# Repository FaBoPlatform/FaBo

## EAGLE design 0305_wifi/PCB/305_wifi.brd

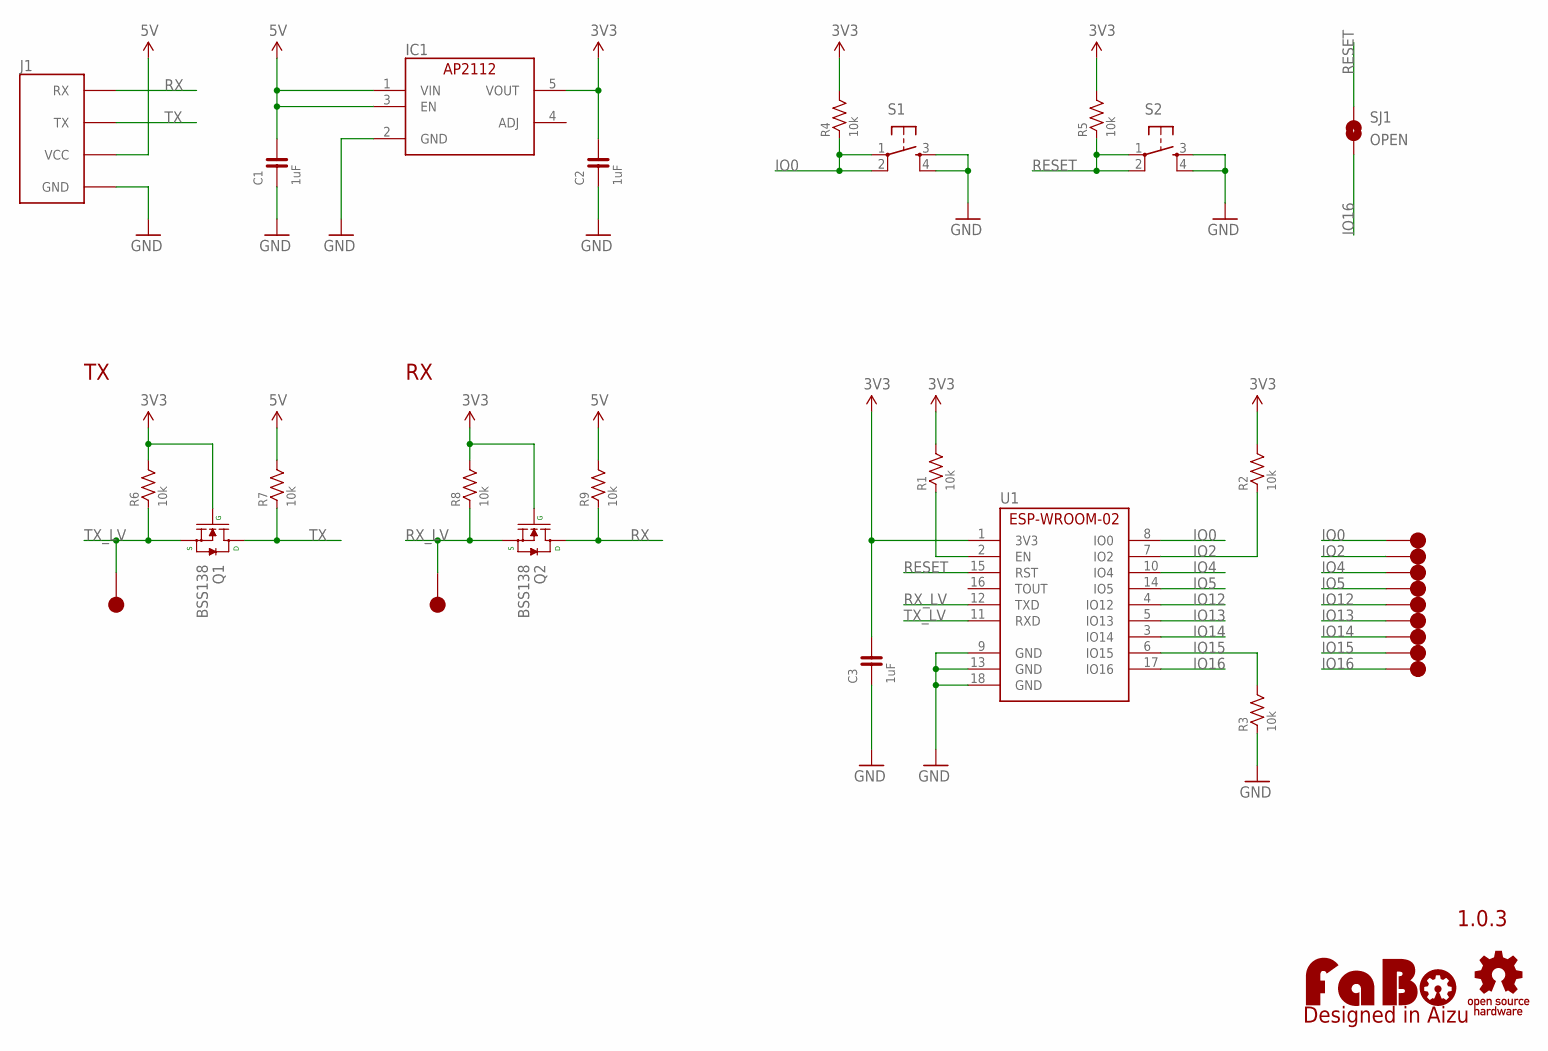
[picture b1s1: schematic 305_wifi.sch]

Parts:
C1, C2, C3: 1uF; 0603
IC1: AP2112K-3.3TRG1; SOT-23-5
J1: FABO_BRICK_SERIAL-2_HOLE; FABO_BRICK_SERIAL_2HOLE
LOGO1: LOGO_FABO-M_BOTTOM; LOGO_FABO_M_BOTTOM
Q1, Q2: BSS138; SOT23-3
R1, R2, R3, R4, R5: 10k; 0603
R6, R7, R8, R9: 10k; 0603-NARROW
S1, S2: TACT-SWITCH-SMD_KMR2; KMR2
SJ1: OPEN; SMD-JUMPER-2-OPEN
TP1, TP2, TP3, TP4, TP5, TP6, TP7, TP8, TP9, TP10, TP11: TP-15
U1: ES-ESPWROOM02
U$1: LOGO_OSHW-M_BOTTOM; LOGO_OSHW_M_BOTTOM

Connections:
3V3: C2.2, C3.2, IC1.5 (VOUT), Q1.1 (G), Q2.1 (G), R1.2, R2.2, R4.2, R5.2, R6.2, R8.2, U1.1 (3V3)
5V: C1.2, IC1.1 (VIN), IC1.3 (EN), J1.VCC, R7.2, R9.2
EN: R1.1, U1.2 (EN)
GND: C1.1, C2.1, C3.1, IC1.2 (GND), J1.GND, R3.1, S1.3, S1.4, S2.3, S2.4, U1.9 (GND), U1.13 (GND), U1.18 (GND)
IO0: R4.1, S1.1, S1.2, TP1.1, U1.8 (IO0)
IO2: R2.1, TP2.1, U1.7 (IO2)
IO4: TP3.1, U1.10 (IO4)
IO5: TP4.1, U1.14 (IO5)
IO12: TP5.1, U1.4 (IO12)
IO13: TP6.1, U1.5 (IO13)
IO14: TP7.1, U1.3 (IO14)
IO15: R3.2, TP8.1, U1.6 (IO15)
IO16: SJ1.2, TP9.1, U1.17 (IO16)
RESET: R5.1, S2.1, S2.2, SJ1.1, U1.15 (RST)
RX: J1.RX, Q2.3 (D), R9.1
RX_LV: Q2.2 (S), R8.1, TP10.1, U1.12 (TXD)
TX: J1.TX, Q1.3 (D), R7.1
TX_LV: Q1.2 (S), R6.1, TP11.1, U1.11 (RXD)

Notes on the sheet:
1.0.3

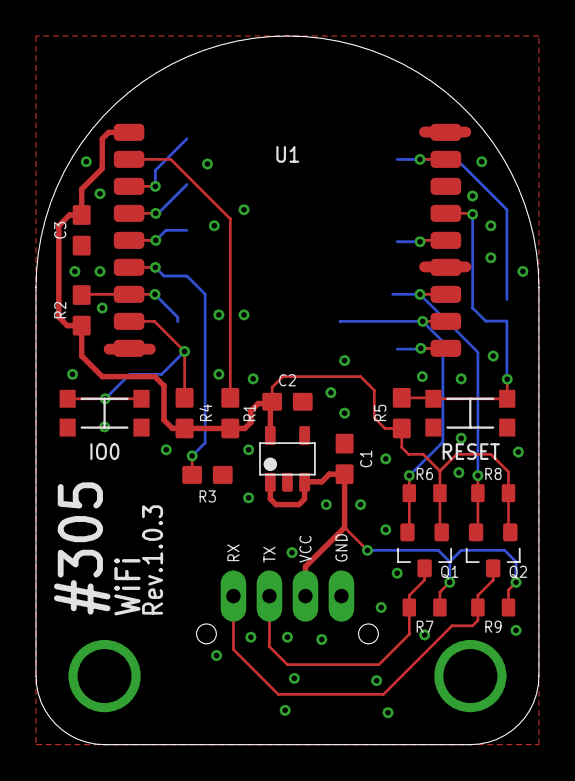
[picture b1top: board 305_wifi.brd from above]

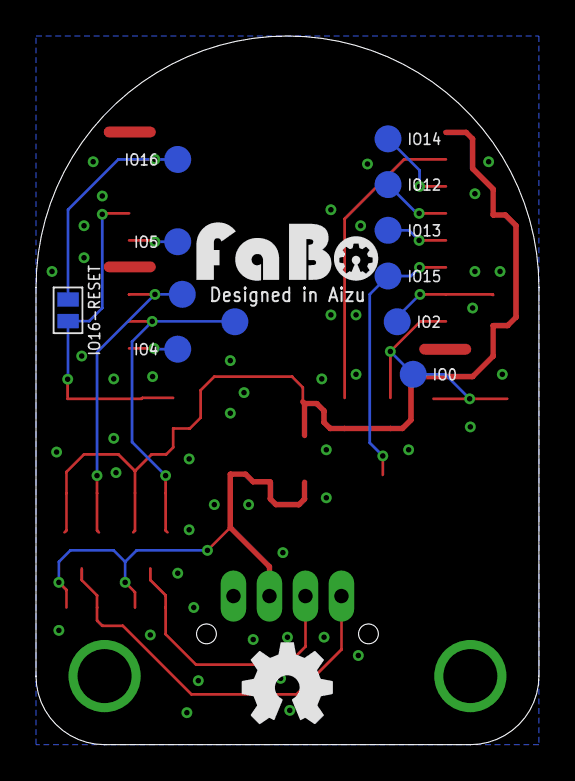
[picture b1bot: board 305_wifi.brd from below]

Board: 2 copper layers, 27.9 x 39.4 mm, 33 parts (12 on the bottom side), 18 nets.

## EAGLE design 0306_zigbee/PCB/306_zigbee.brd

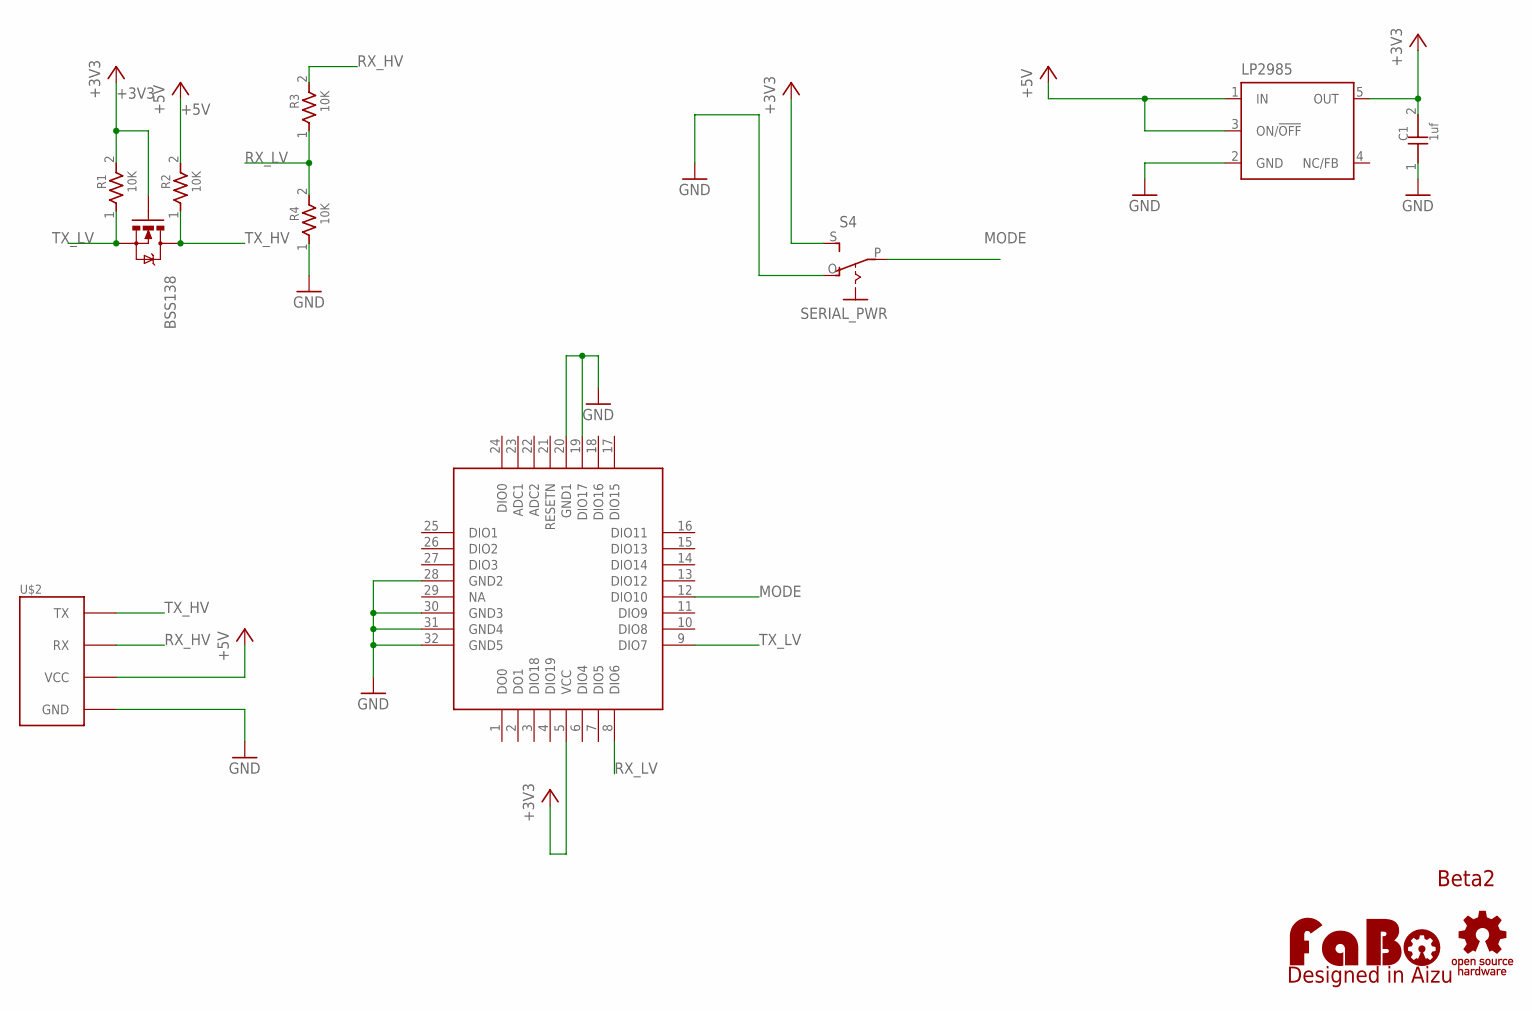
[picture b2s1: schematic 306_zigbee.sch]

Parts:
BSS138: MOSFET-NCHANNELSMD; SOT23-3
C1: 1uf; 0603
LOGO1: LOGO_FABO-M; LOGO_FABO_M
LP2985: LP2985-XXDBVR33; SOT23-DBV
R1, R2, R3, R4: 10K; 0603
S4: SERIAL_PWR; EG1218
U$2: BRICK_SERIAL
U$3: TOCOS-TWE001L
U$4: LOGO_OSHW-M_BOTTOM; LOGO_OSHW_M_BOTTOM

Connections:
+3V3: BSS138.1 (G), C1.2, LP2985.5 (OUT), R1.2, S4.S, U$3.5 (VCC)
+5V: LP2985.1 (IN), LP2985.3 (ON/!OFF), R2.2, U$2.VCC
GND: C1.1, LP2985.2 (GND), R4.1, S4.O, U$2.GND, U$3.19 (DIO17), U$3.20 (GND1), U$3.28 (GND2), U$3.30 (GND3), U$3.31 (GND4), U$3.32 (GND5)
MODE: S4.P, U$3.12 (DIO10)
RX_HV: R3.2, U$2.RX
RX_LV: R3.1, R4.2, U$3.8 (DIO6)
TX_HV: BSS138.3 (D), R2.1, U$2.TX
TX_LV: BSS138.2 (S), R1.1, U$3.9 (DIO7)

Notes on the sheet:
Beta2

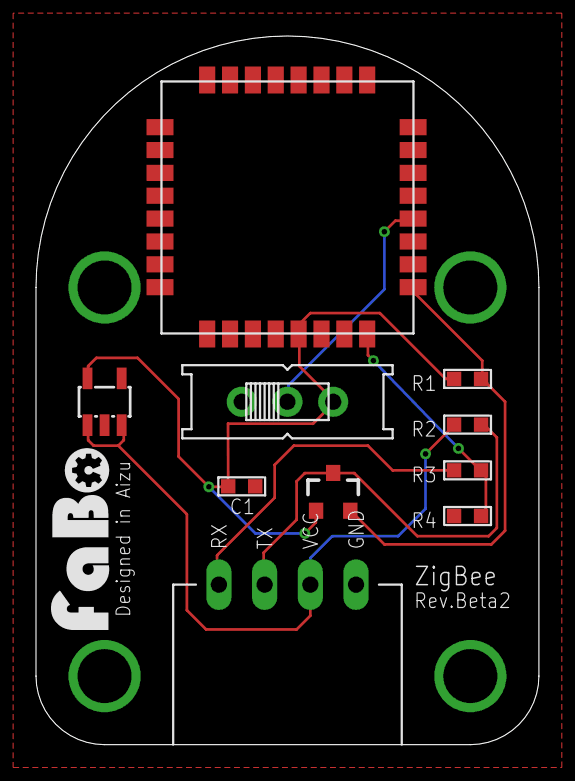
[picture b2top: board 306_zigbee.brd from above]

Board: 2 copper layers, 27.9 x 39.4 mm, 12 parts (0 on the bottom side), 8 nets.

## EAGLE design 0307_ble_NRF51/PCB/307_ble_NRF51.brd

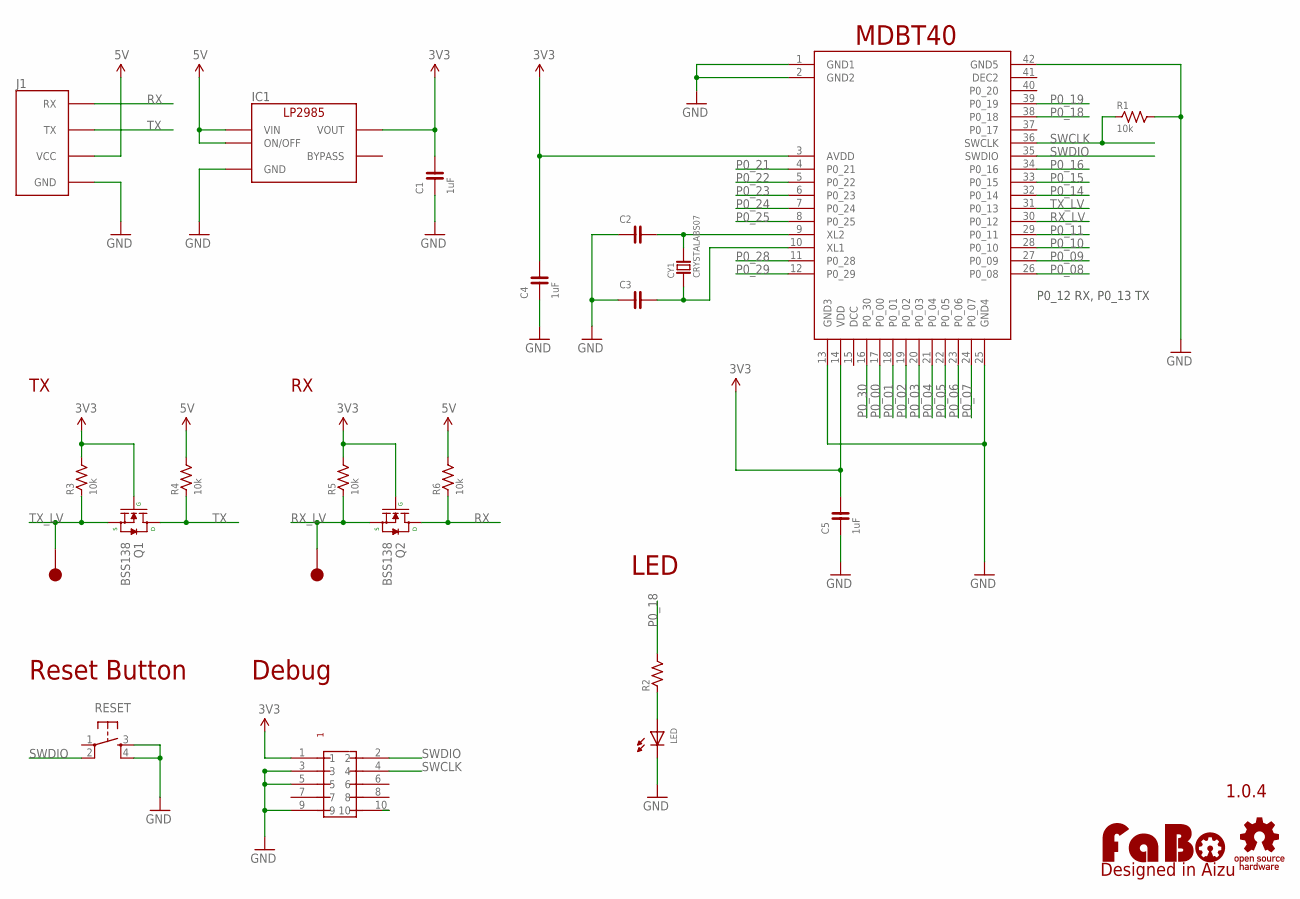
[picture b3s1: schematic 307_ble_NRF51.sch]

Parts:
C1, C4, C5: 1uF; 0603-NARROW
C2, C3: CAPACITOR-0603_NARROW; 0603-NARROW
CY1: CRYSTALABS07; ABRACOM-ABS07-32.768KHZ
IC1: LP2985-33DBV; SOT-23-5
J1: FABO_BRICK_SERIAL
LED: LED-0603; 0603
LOGO1: LOGO_FABO-M_BOTTOM; LOGO_FABO_M_BOTTOM
Q1, Q2: BSS138; SOT23-3
R1, R3, R4, R5, R6: 10k; 0603-NARROW
R2: RESISTOR-0603-NARROW; 0603-NARROW
RESET: TACT-SWITCH-SMD_KMR2; KMR2
TP10, TP11: TP-15
U$2: LOGO_OSHW-M_BOTTOM; LOGO_OSHW_M_BOTTOM
U$7: RAYTAC-MDBT40
U$8: PIN-HEADER-SMT(1.27MM)2X5

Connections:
3V3: C1.2, C4.2, C5.2, IC1.5 (VOUT), Q1.1 (G), Q2.1 (G), R3.2, R5.2, U$7.3 (AVDD), U$7.14 (VDD), U$8.1
5V: IC1.1 (VIN), IC1.3 (ON/OFF), J1.VCC, R4.2, R6.2
GND: C1.1, C2.1, C3.1, C4.1, C5.1, IC1.2 (GND), J1.GND, LED.CATHODE, R1.2, RESET.3, RESET.4, U$7.1 (GND1), U$7.2 (GND2), U$7.13 (GND3), U$7.25 (GND4), U$7.42 (GND5), U$8.3, U$8.5, U$8.9
unnamed: LED.ANODE, R2.1
unnamed: C2.2, CY1.P$2, U$7.9 (XL2)
unnamed: C3.2, CY1.P$1, U$7.10 (XL1)
P0_00: U$7.17 (P0_00)
P0_01: U$7.18 (P0_01)
P0_02: U$7.19 (P0_02)
P0_03: U$7.20 (P0_03)
P0_04: U$7.21 (P0_04)
P0_05: U$7.22 (P0_05)
P0_06: U$7.23 (P0_06)
P0_07: U$7.24 (P0_07)
P0_08: U$7.26 (P0_08)
P0_09: U$7.27 (P0_09)
P0_10: U$7.28 (P0_10)
P0_11: U$7.29 (P0_11)
P0_14: U$7.32 (P0_14)
P0_15: U$7.33 (P0_15)
P0_16: U$7.34 (P0_16)
P0_18: R2.2, U$7.38 (P0_18)
P0_19: U$7.39 (P0_19)
P0_21: U$7.4 (P0_21)
P0_22: U$7.5 (P0_22)
P0_23: U$7.6 (P0_23)
P0_24: U$7.7 (P0_24)
P0_25: U$7.8 (P0_25)
P0_28: U$7.11 (P0_28)
P0_29: U$7.12 (P0_29)
P0_30: U$7.16 (P0_30)
RESET: U$8.10
RX: J1.RX, Q2.3 (D), R6.1
RX_LV: Q2.2 (S), R5.1, TP10.1, U$7.30 (P0_12)
SWCLK: R1.1, U$7.36 (SWCLK), U$8.4
SWDIO: RESET.2, U$7.35 (SWDIO), U$8.2
TX: J1.TX, Q1.3 (D), R4.1
TX_LV: Q1.2 (S), R3.1, TP11.1, U$7.31 (P0_13)

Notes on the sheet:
1.0.4
Reset Button
MDBT40
LED
Debug
P0_12 RX, P0_13 TX

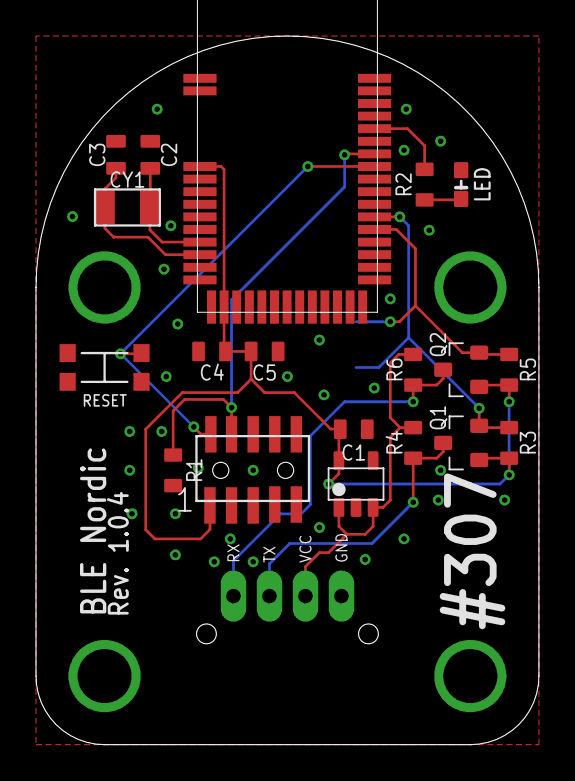
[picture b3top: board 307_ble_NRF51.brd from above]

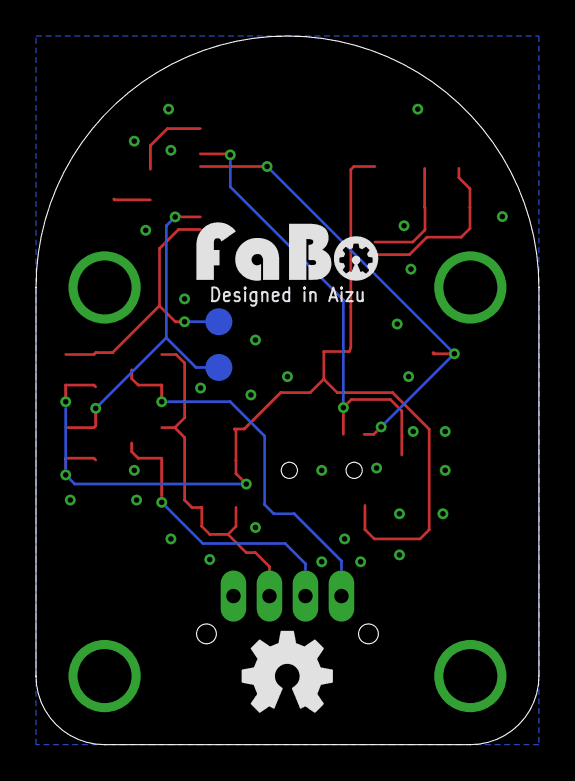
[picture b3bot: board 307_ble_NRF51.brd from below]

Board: 2 copper layers, 27.9 x 39.4 mm, 24 parts (2 on the bottom side), 13 nets.

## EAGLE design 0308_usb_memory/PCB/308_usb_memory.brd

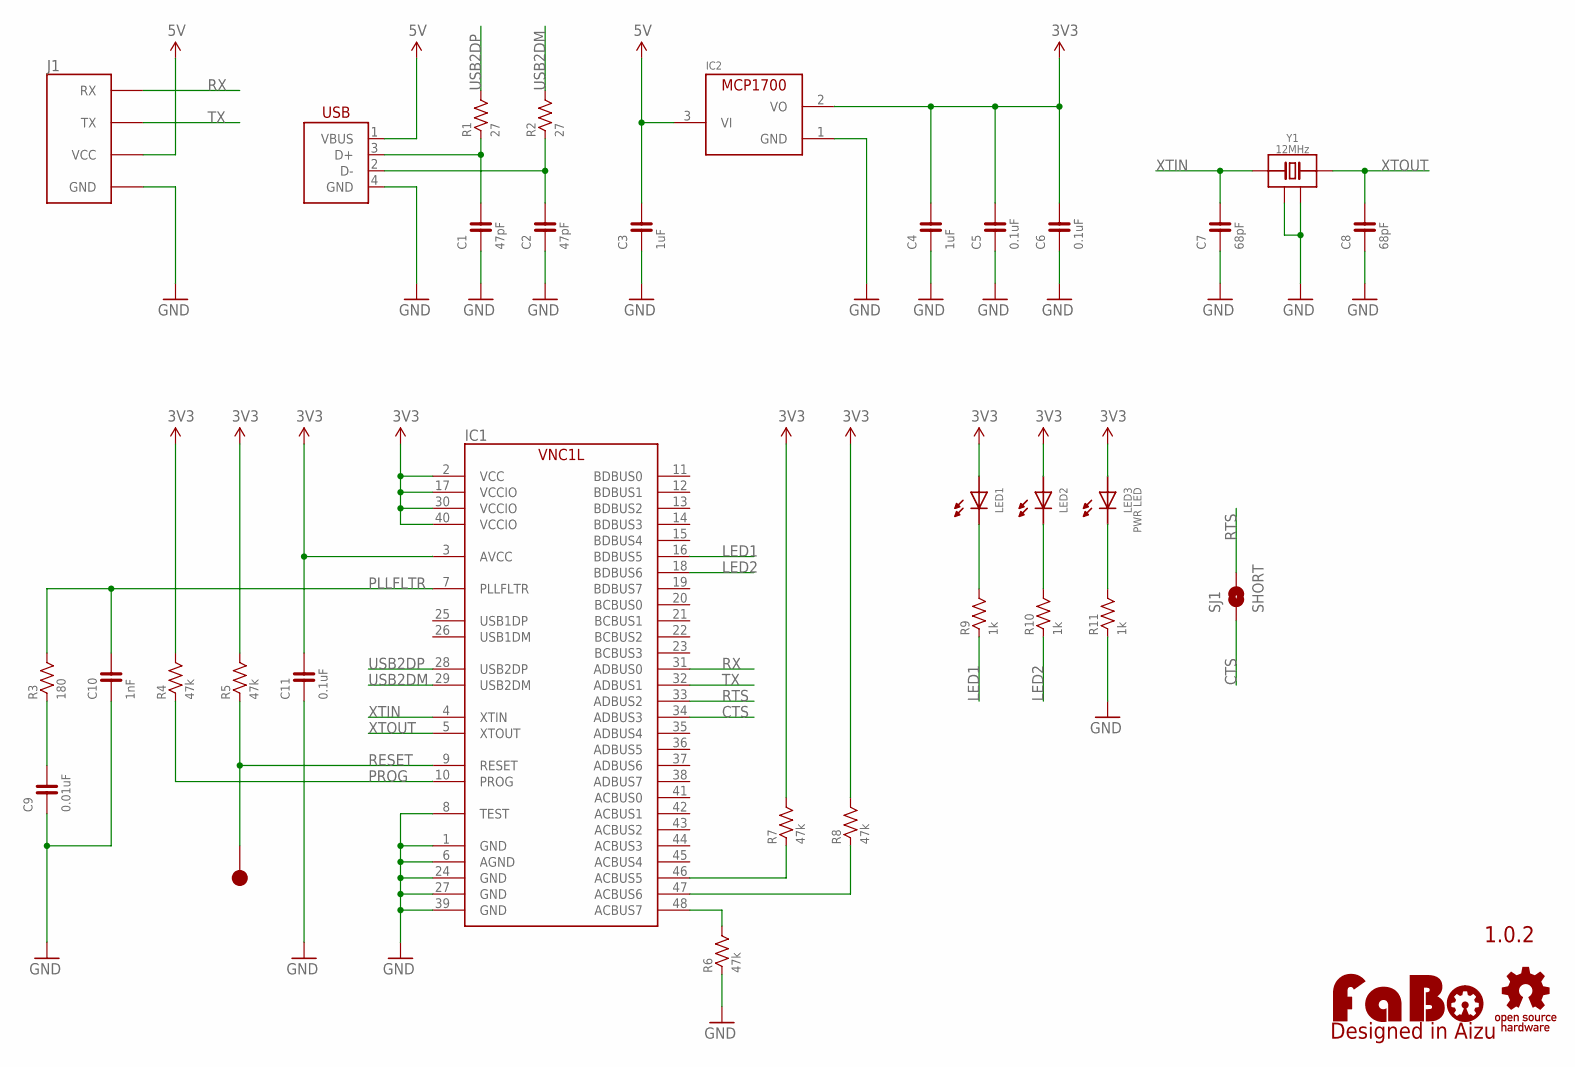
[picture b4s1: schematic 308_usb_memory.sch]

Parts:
C1, C2: 47pF; 0603-NARROW
C3, C4: 1uF; 0603-NARROW
C5, C6, C11: 0.1uF; 0603-NARROW
C7, C8: 68pF; 0603-NARROW
C9: 0.01uF; 0603-NARROW
C10: 1nF; 0603-NARROW
IC1: VNC1L-1A; LQFP-48
IC2: MCP1700T-3302TT; SOT-23
J1: FABO_BRICK_SERIAL-2_HOLE; FABO_BRICK_SERIAL_2HOLE
LED1, LED2: LED-0603-NARROW; 0603-NARROW
LED3: PWR LED; 0603-NARROW
LOGO1: LOGO_FABO-M_BOTTOM; LOGO_FABO_M_BOTTOM
R1, R2: 27; 0603-NARROW
R3: 180; 0603-NARROW
R4, R5, R6, R7, R8: 47k; 0603-NARROW
R9, R10, R11: 1k; 0603-NARROW
SJ1: SHORT; SMD-JUMPER-2-SHORT
TP1: TP-15
U$2: LOGO_OSHW-M_BOTTOM; LOGO_OSHW_M_BOTTOM
USB1: USB-B_PTH; USB-4AF103BS
Y1: 12MHz; ECS-12MHZ

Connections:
3V3: C4.2, C5.2, C6.2, C11.2, IC1.2 (VCC), IC1.3 (AVCC), IC1.17 (VCCIO), IC1.30 (VCCIO), IC1.40 (VCCIO), IC2.2 (VO), LED1.ANODE, LED2.ANODE, LED3.ANODE, R4.2, R5.2, R7.2, R8.2
5V: C3.2, IC2.3 (VI), J1.VCC, USB1.1 (VBUS)
ACBUS5: IC1.46 (ACBUS5), R7.1
ACBUS6: IC1.47 (ACBUS6), R8.1
ACBUS7: IC1.48 (ACBUS7), R6.2
CTS: IC1.34 (ADBUS3), SJ1.2
GND: C1.1, C2.1, C3.1, C4.1, C5.1, C6.1, C7.1, C8.1, C9.1, C10.1, C11.1, IC1.1 (GND), IC1.6 (AGND), IC1.8 (TEST), IC1.24 (GND), IC1.27 (GND), IC1.39 (GND), IC2.1 (GND), J1.GND, R6.1, R11.1, USB1.4 (GND), Y1.2 (GND), Y1.4 (GND)
LED1: IC1.16 (BDBUS5), R9.1
LED2: IC1.18 (BDBUS6), R10.1
unnamed: C9.2, R3.1
unnamed: C1.2, R1.1, USB1.3 (D+)
unnamed: C2.2, R2.1, USB1.2 (D-)
unnamed: LED2.CATHODE, R10.2
unnamed: LED1.CATHODE, R9.2
unnamed: LED3.CATHODE, R11.2
PLLFLTR: C10.2, IC1.7 (PLLFLTR), R3.2
PROG: IC1.10 (PROG), R4.1
RESET: IC1.9 (RESET), R5.1, TP1.1
RTS: IC1.33 (ADBUS2), SJ1.1
RX: IC1.31 (ADBUS0), J1.RX
TX: IC1.32 (ADBUS1), J1.TX
USB2DM: IC1.29 (USB2DM), R2.2
USB2DP: IC1.28 (USB2DP), R1.2
XTIN: C7.2, IC1.4 (XTIN), Y1.1 (IO)
XTOUT: C8.2, IC1.5 (XTOUT), Y1.3 (IO)

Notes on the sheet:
1.0.2

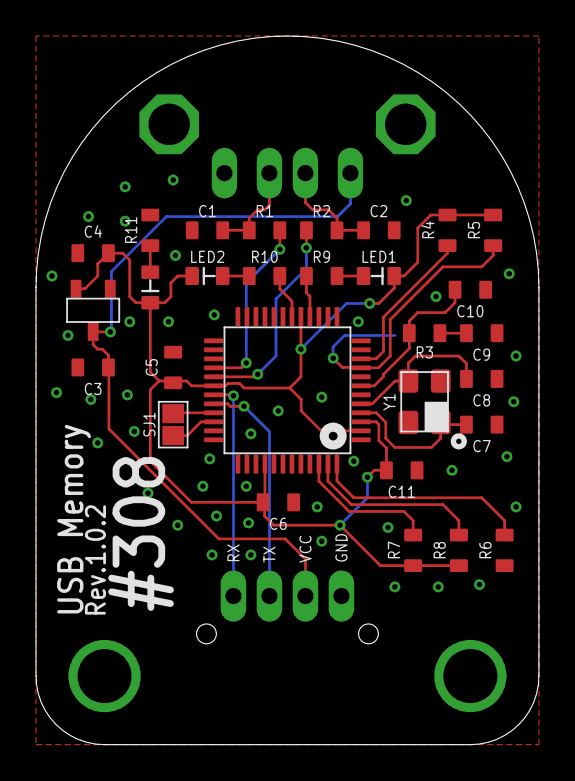
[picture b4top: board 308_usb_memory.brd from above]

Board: 2 copper layers, 27.9 x 39.4 mm, 34 parts (1 on the bottom side), 25 nets.

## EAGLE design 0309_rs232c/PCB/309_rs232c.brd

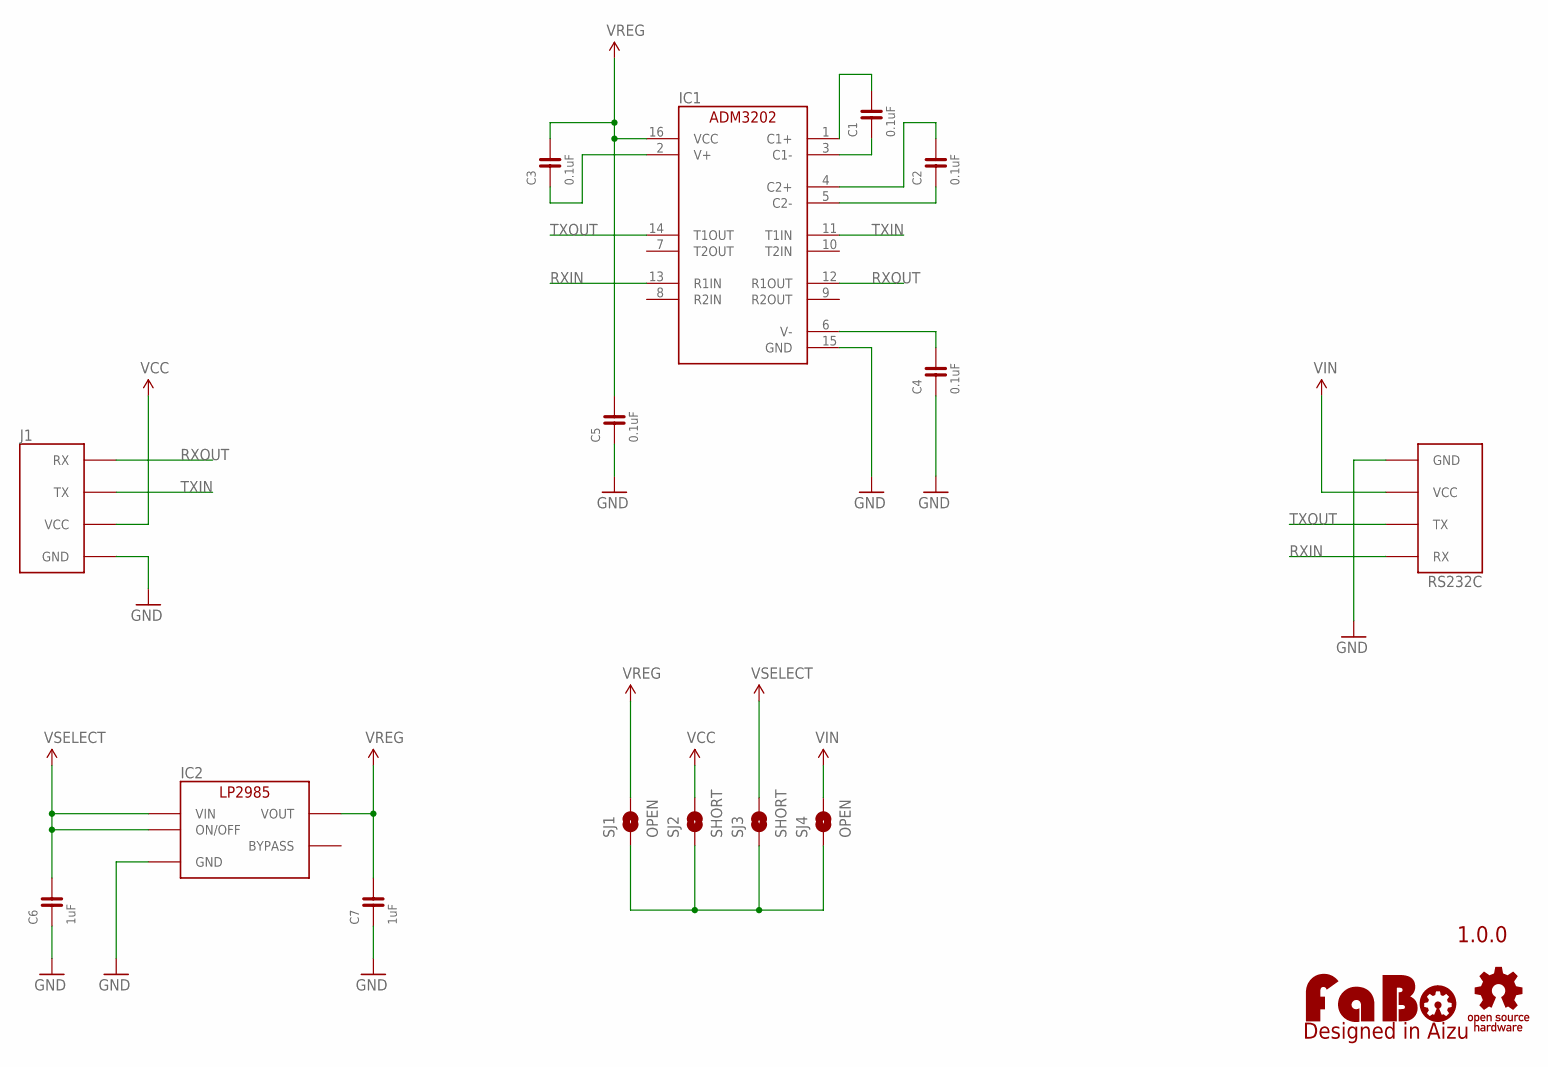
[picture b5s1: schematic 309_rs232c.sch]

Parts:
C1, C2, C3, C4, C5: 0.1uF; 0603-NARROW
C6, C7: 1uF; 0603-NARROW
IC1: ADM3202ARU; TSSOP-16
IC2: LP2985-33DBV; SOT-23-5
J1: FABO_BRICK_SERIAL
LOGO1: LOGO_FABO-M_BOTTOM; LOGO_FABO_M_BOTTOM
RS232C: FABO_BRICK_SERIAL-S04B-PASK-2_LONG; FABO_BRICK_SERIAL_S04B-PASK-2_LONG
SJ1, SJ4: OPEN; SMD-JUMPER-2-OPEN
SJ2, SJ3: SHORT; SMD-JUMPER-2-SHORT
U$2: LOGO_OSHW-M_BOTTOM; LOGO_OSHW_M_BOTTOM

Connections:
GND: C4.1, C5.1, C6.1, C7.1, IC1.15 (GND), IC2.2 (GND), J1.GND, RS232C.GND
unnamed: SJ1.2, SJ2.2, SJ3.2, SJ4.2
unnamed: C1.1, IC1.3 (C1-)
unnamed: C1.2, IC1.1 (C1+)
unnamed: C2.1, IC1.5 (C2-)
unnamed: C2.2, IC1.4 (C2+)
unnamed: C3.1, IC1.2 (V+)
unnamed: C4.2, IC1.6 (V-)
RXIN: IC1.13 (R1IN), RS232C.RX
RXOUT: IC1.12 (R1OUT), J1.RX
TXIN: IC1.11 (T1IN), J1.TX
TXOUT: IC1.14 (T1OUT), RS232C.TX
VCC: J1.VCC, SJ2.1
VIN: RS232C.VCC, SJ4.1
VREG: C3.2, C5.2, C7.2, IC1.16 (VCC), IC2.5 (VOUT), SJ1.1
VSELECT: C6.2, IC2.1 (VIN), IC2.3 (ON/OFF), SJ3.1

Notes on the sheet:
1.0.0

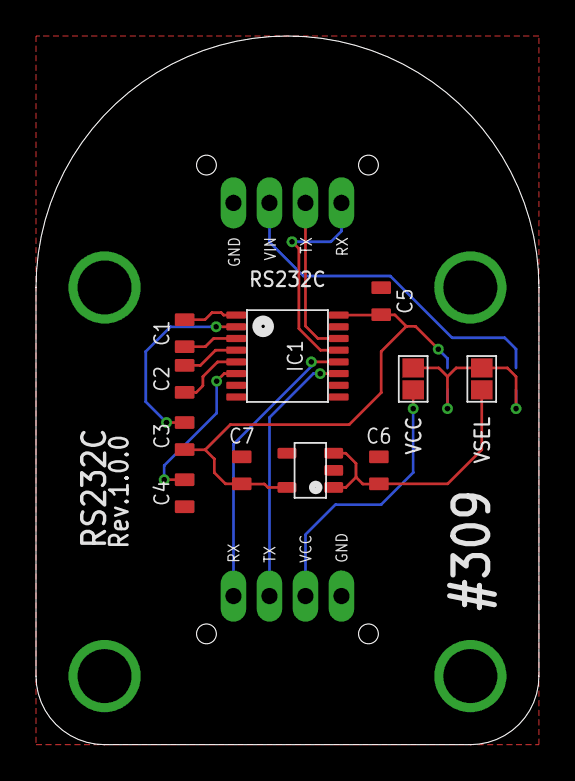
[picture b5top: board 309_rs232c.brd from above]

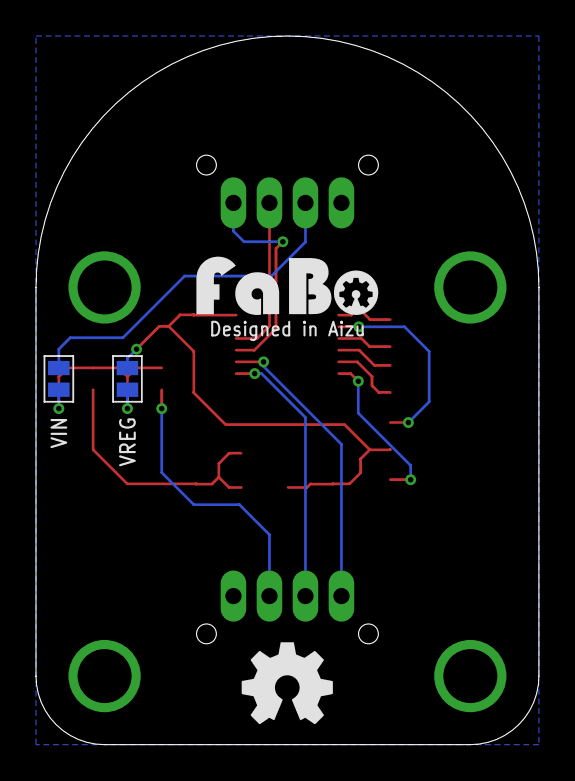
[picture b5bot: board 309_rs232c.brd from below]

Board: 2 copper layers, 27.9 x 39.4 mm, 17 parts (2 on the bottom side), 16 nets.

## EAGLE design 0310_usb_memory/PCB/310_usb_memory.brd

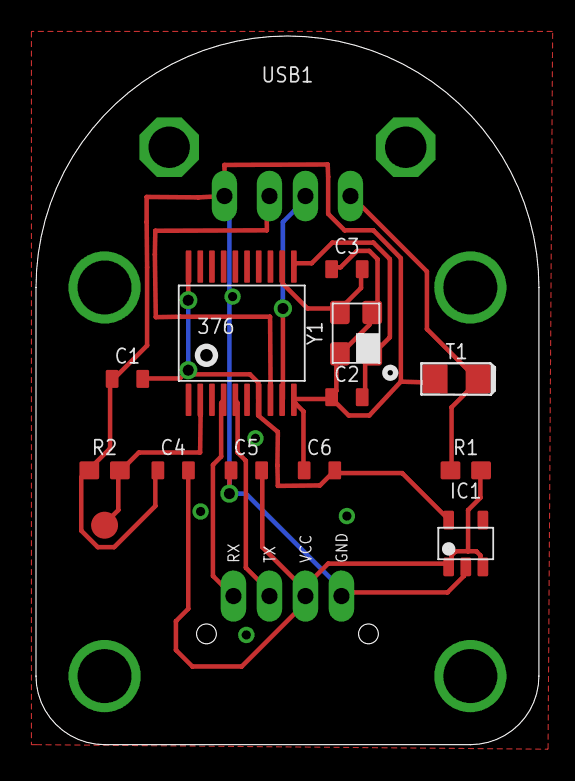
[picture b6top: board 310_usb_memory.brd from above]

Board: 2 copper layers, 27.9 x 39.4 mm, 15 parts (0 on the bottom side), 11 nets.

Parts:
376: CH376T; SSOP-20
C1, C5, C6: 0.1uF; 0603-NARROW
C2, C3: 22pF; 0603-NARROW
C4: 10uF; 0603-NARROW
IC1: SOT-23-5
J1: FABO_BRICK_SERIAL
R1: 2; 0603
R2: 4.7K; 0603
T1: 10uF; 1206-TANTULM
TP1: TP-15
USB1: USB-4AF103BS
Y1: 12MHz; ECS-12MHZ

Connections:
3V3: 376.7, 376.20, C1.2, C6.2, IC1.5
5V: C4.2, C5.2, IC1.1, IC1.3, J1.VCC, R1.2
D+: 376.8, USB1.3
D-: 376.9, USB1.2
GND: 376.10, C1.1, C2.1, C3.1, C4.1, C5.1, C6.1, IC1.2, J1.GND, R2.1, T1.-, USB1.4, Y1.2, Y1.4
unnamed: R1.1, T1.+, USB1.1
RESET: 376.2, R2.2, TP1.1
RX: 376.4, J1.RX
TX: 376.5, J1.TX
XTIN: 376.11, C2.2, Y1.1
XTOUT: 376.12, C3.2, Y1.3

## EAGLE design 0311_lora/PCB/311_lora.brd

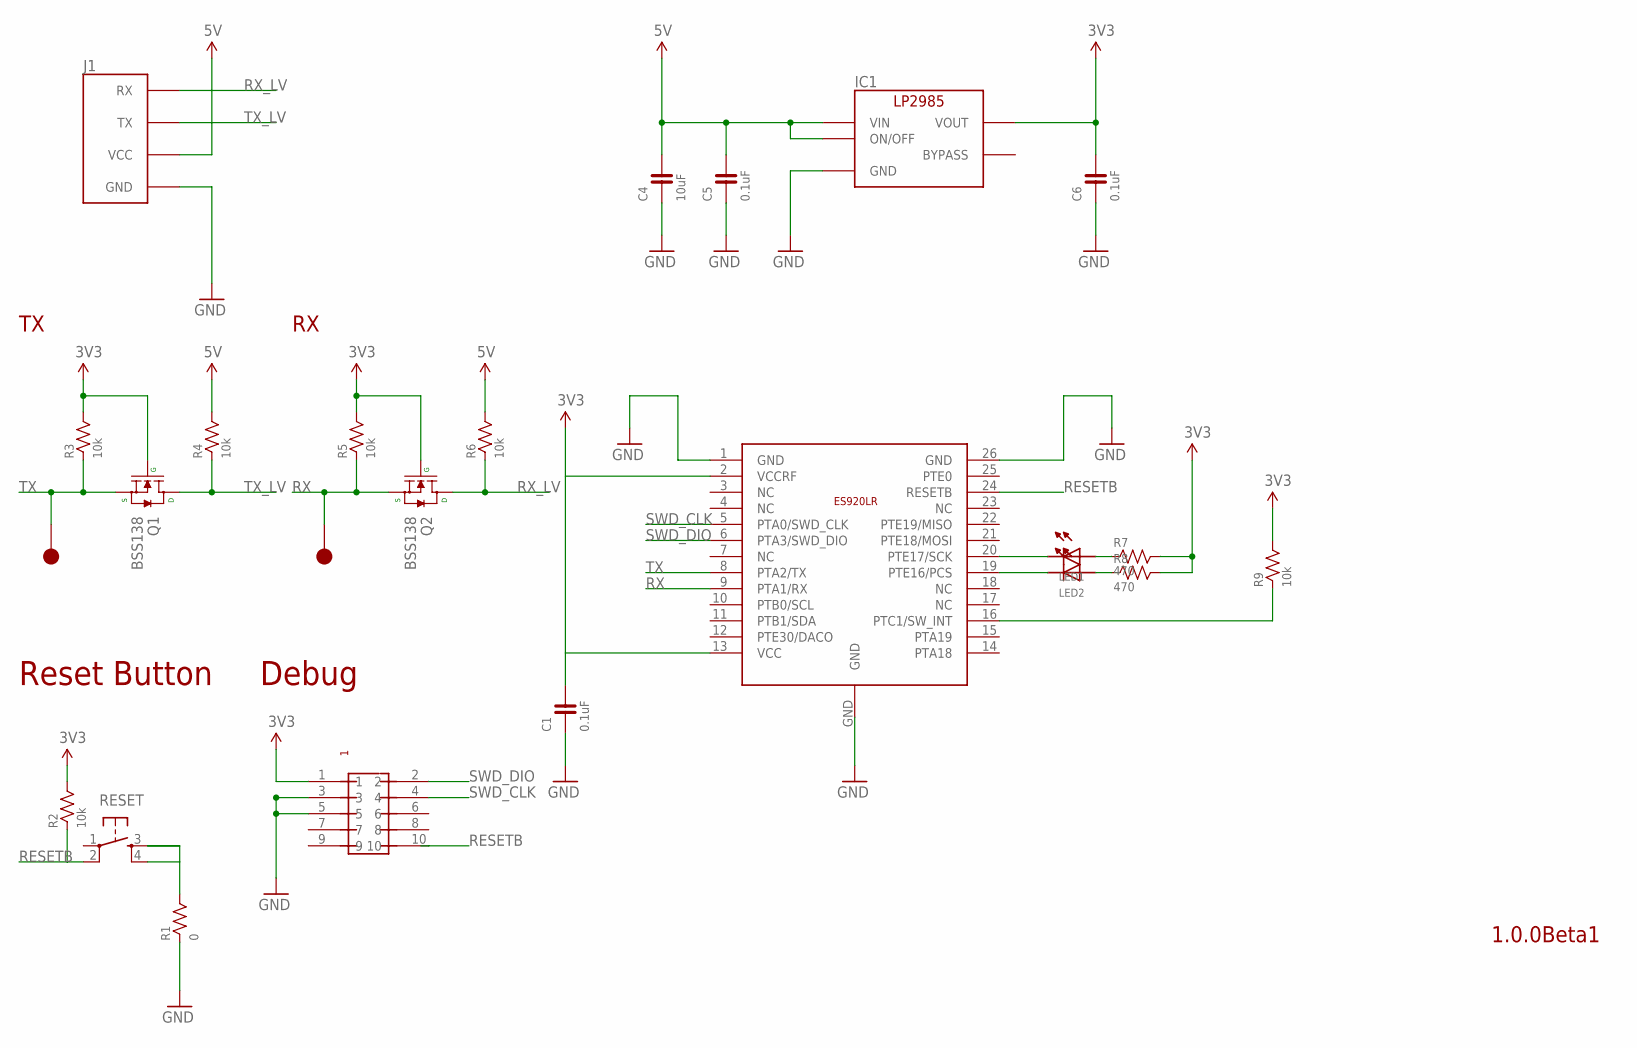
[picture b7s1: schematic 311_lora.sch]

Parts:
C1, C5, C6: 0.1uF; 0603-NARROW
C4: 10uF; 0603-NARROW
IC1: LP2985-33DBV; SOT-23-5
J1: FABO_BRICK_SERIAL-LONGER; FABO_BRICK_SERIAL_LONGER
LED1, LED2: LED-0603; 0603
Q1, Q2: BSS138; SOT23-3
R1: 0; 0603-NARROW
R2, R3, R4, R5, R6, R9: 10k; 0603-NARROW
R7, R8: 470; 0603-NARROW
RESET: TACT-SWITCH-SMD_KMR2; KMR2
TP10, TP11: TP-15
U$2: ES920LR
U$8: PIN-HEADER-SMT(1.27MM)2X5

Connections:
3V3: C1.2, C6.2, IC1.5 (VOUT), Q1.1 (G), Q2.1 (G), R2.2, R3.2, R5.2, R7.2, R8.2, R9.2, U$2.2 (VCCRF), U$2.13 (VCC), U$8.1
5V: C4.2, C5.2, IC1.1 (VIN), IC1.3 (ON/OFF), J1.VCC, R4.2, R6.2
GND: C1.1, C4.1, C5.1, C6.1, IC1.2 (GND), J1.GND, R1.1, U$2.1 (GND), U$2.26 (GND), U$2.GND, U$8.3, U$8.5
unnamed: R1.2, RESET.3, RESET.4
unnamed: LED2.CATHODE, U$2.19 (PTE16/PCS)
unnamed: LED1.CATHODE, U$2.20 (PTE17/SCK)
unnamed: LED1.ANODE, R7.1
unnamed: LED2.ANODE, R8.1
unnamed: R9.1, U$2.16 (PTC1/SW_INT)
RESETB: R2.1, RESET.2, U$2.24 (RESETB), U$8.10
RX: Q2.2 (S), R5.1, TP10.1, U$2.9 (PTA1/RX)
RX_LV: J1.RX, Q2.3 (D), R6.1
SWD_CLK: U$2.5 (PTA0/SWD_CLK), U$8.4
SWD_DIO: U$2.6 (PTA3/SWD_DIO), U$8.2
TX: Q1.2 (S), R3.1, TP11.1, U$2.8 (PTA2/TX)
TX_LV: J1.TX, Q1.3 (D), R4.1

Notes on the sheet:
1.0.0Beta1
Reset Button
Debug

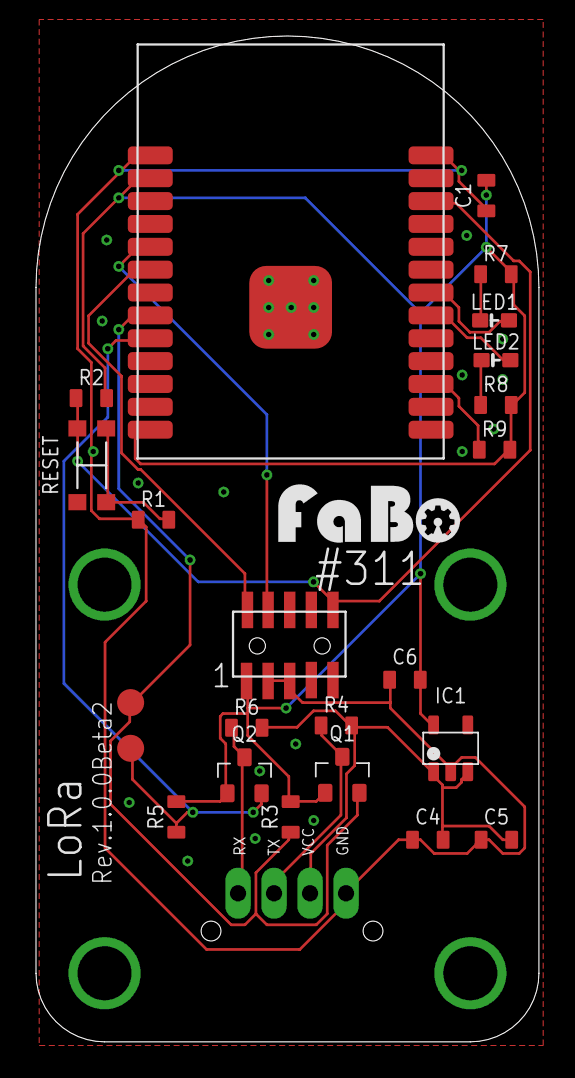
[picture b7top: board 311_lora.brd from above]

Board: 2 copper layers, 27.9 x 55.9 mm, 25 parts (0 on the bottom side), 16 nets.

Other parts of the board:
U$3: LOGO_FABO_MS

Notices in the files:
parts and their libraries:
FaBo-Supply: Released under the Creative Commons Attribution-ShareAlike 4.0 License
https://creativecommons.org/licenses/by-sa/4.0
FaBo-etc: Released under the Creative Commons
SparkFun: Licensing: CC v3.0 Share-Alike You are welcome to use this library for commercial purposes.
